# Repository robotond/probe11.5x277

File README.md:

# probe11.5x277
Probe pcb for 277mm raster dryer / 16 pcb-s, 8 sensors

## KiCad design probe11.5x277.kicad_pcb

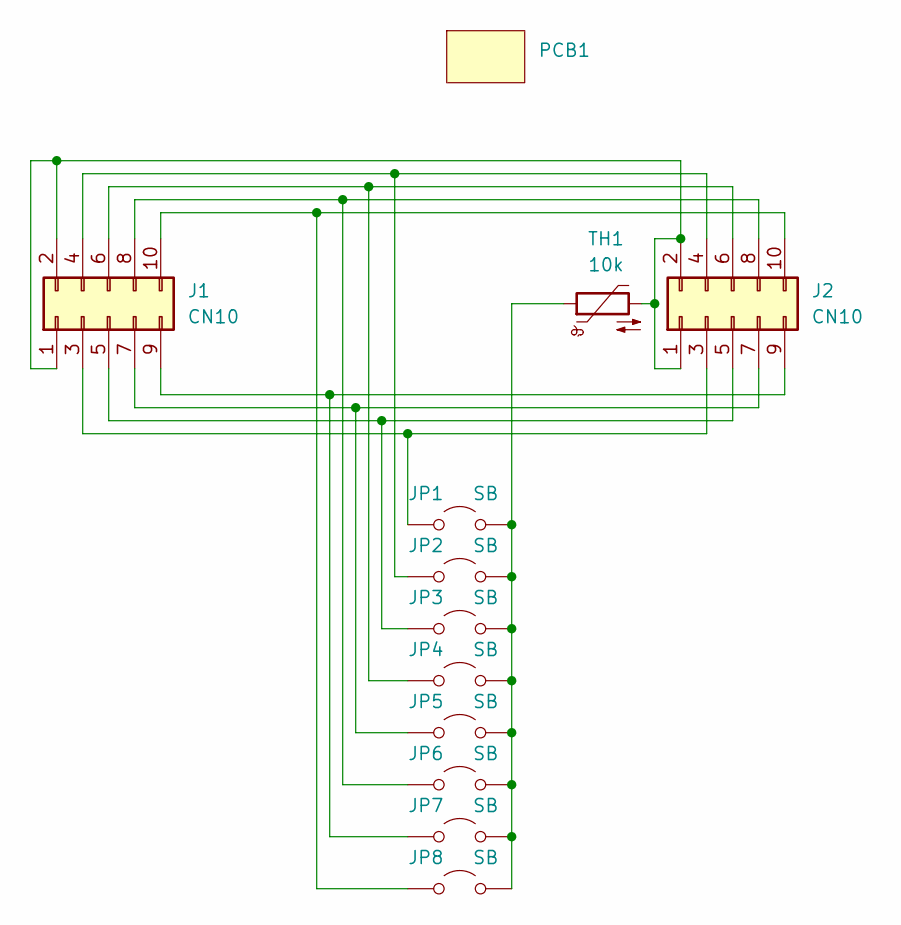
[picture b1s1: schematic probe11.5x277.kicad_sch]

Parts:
J1, J2: CN10; PinHeader_2x05_P2.54mm_Vertical
JP1, JP2, JP3, JP4, JP5, JP6, JP7, JP8: SB; SolderJumper-2_P1.3mm_Open_RoundedPad1.0x1.5mm
PCB1: PCB11x297
TH1: 10k; NTC_5x2

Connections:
unnamed: J1.1, J1.2, J2.1, J2.2, TH1.2
unnamed: J1.3, J2.3, JP1.1 (A)
unnamed: J1.4, J2.4, JP2.1 (A)
unnamed: J1.5, J2.5, JP3.1 (A)
unnamed: J1.6, J2.6, JP4.1 (A)
unnamed: J1.7, J2.7, JP5.1 (A)
unnamed: J1.8, J2.8, JP6.1 (A)
unnamed: J1.9, J2.9, JP7.1 (A)
unnamed: J1.10, J2.10, JP8.1 (A)
unnamed: JP1.2 (B), JP2.2 (B), JP3.2 (B), JP4.2 (B), JP5.2 (B), JP6.2 (B), JP7.2 (B), JP8.2 (B), TH1.1

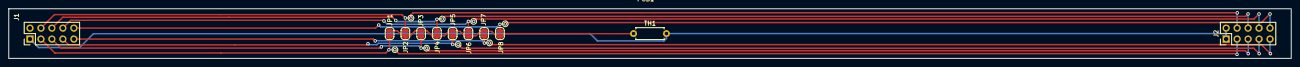
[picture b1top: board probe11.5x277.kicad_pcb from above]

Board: 2 copper layers, 297.0 x 11.5 mm, 12 parts (0 on the bottom side), 10 nets.

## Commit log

2024-05-16 Update .gitignore
    *.lck added
2024-05-16 Silkscreen updated
2024-05-16 3D model files, footprint libs added
2024-05-16 Updated before manufacturing
